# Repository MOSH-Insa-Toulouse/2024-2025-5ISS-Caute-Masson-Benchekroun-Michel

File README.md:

**Repository structure :**
- [LoRa\_module.ino](LoRa_module.ino) : Smart device code, from the logic for using the gas sensor, to the BLE and LoRa connectivity.
- [Shield\_Gas\_Sensor](Shield_Gas_Sensor) : Design of the Arduino UNO shield for the smart device. See the routing [here](Shield_Gas_Sensor/Acquisition_board_aduino_UNO.kicad_pcb), and the schematic [here](Shield_Gas_Sensor/Acquisition_board_aduino_UNO.kicad_sch)
- [Node-RED](Node-RED) : Node RED application code
- [Documentation](Documentation) : Datasheet of the used components
- [The datasheet](Datasheet_Gas_Sensor.pdf) : Datasheet of our gas sensor
- [The project report](MOSH_Report.pdf) : Report of our smart device project, from the manufacturing of the MOx sensor to the design of our node PCB, sensor conditionner and application

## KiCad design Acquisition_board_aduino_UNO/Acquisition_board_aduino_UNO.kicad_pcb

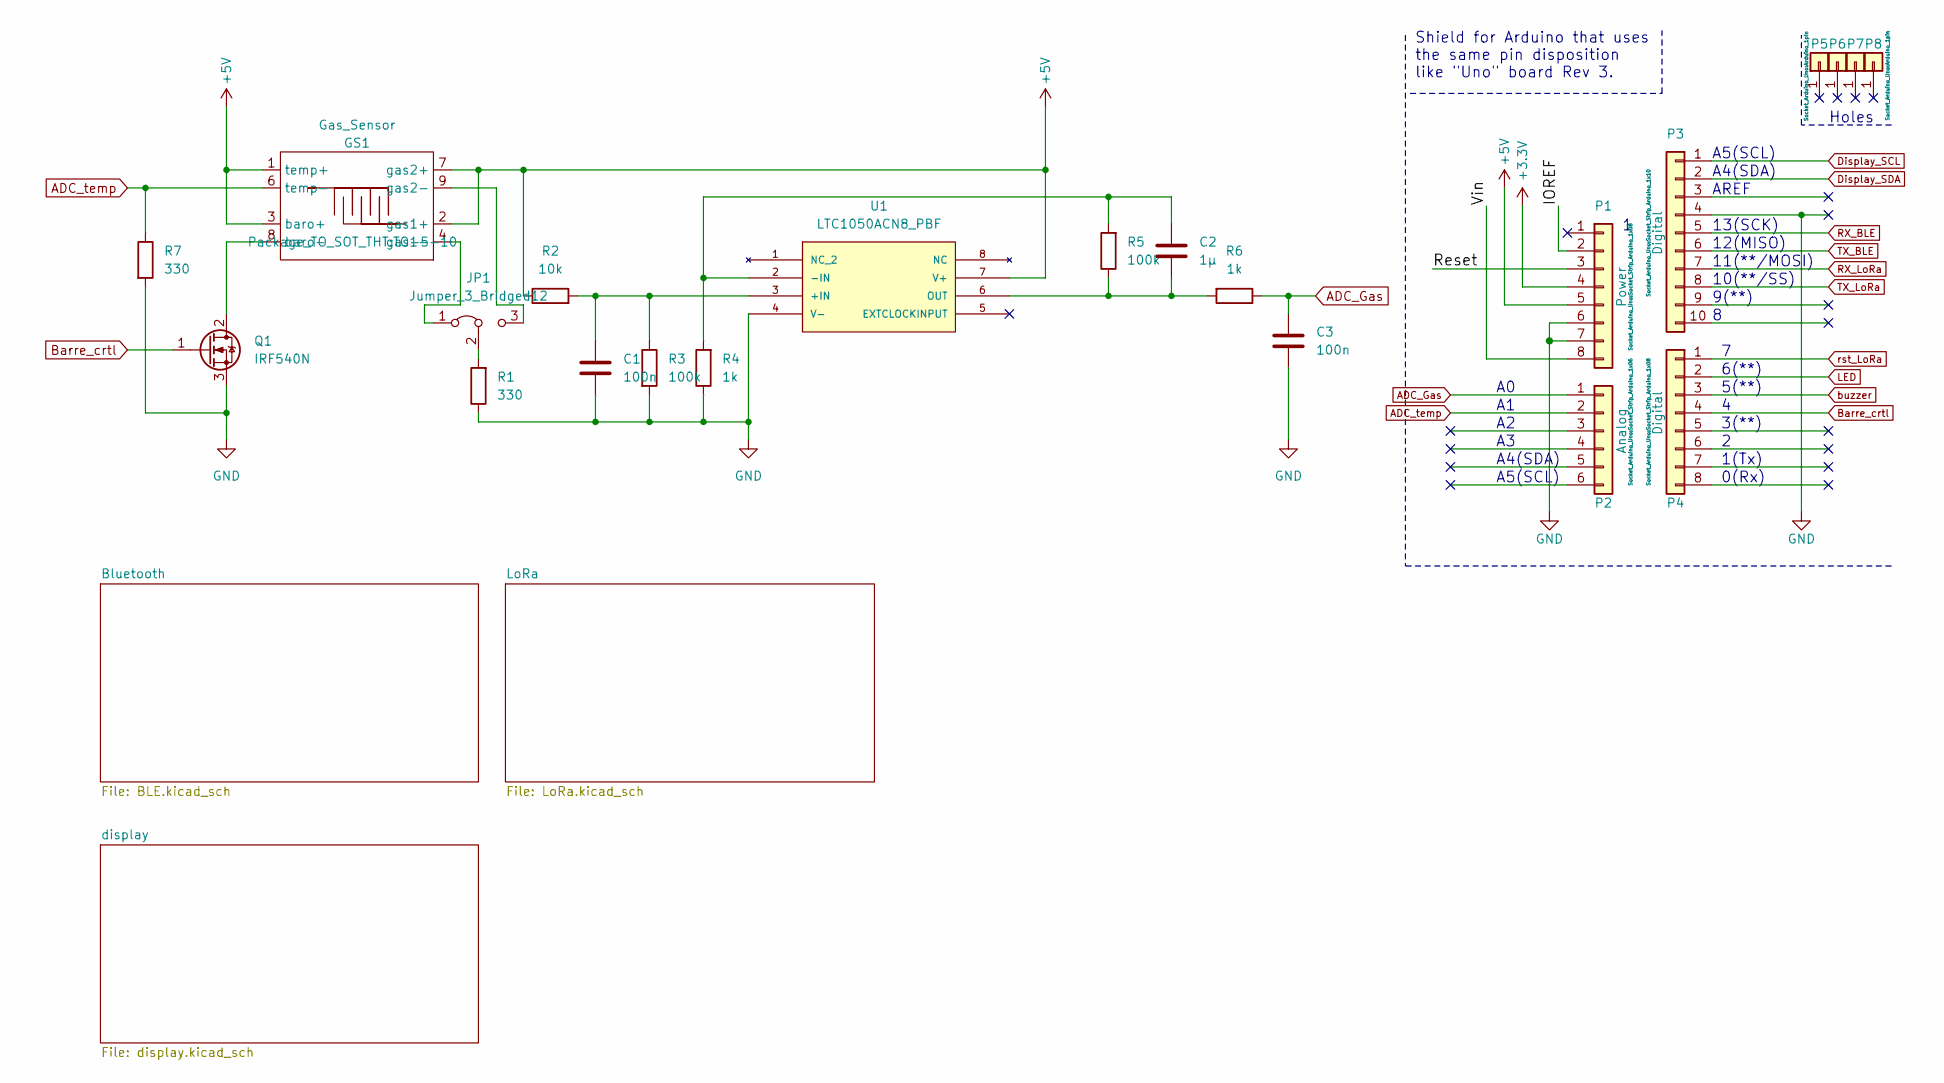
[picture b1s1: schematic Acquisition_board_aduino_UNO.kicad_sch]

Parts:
C1, C3: 100n; C_Disc_D3.0mm_W1.6mm_P2.50mm
C2: 1µ; C_Rect_L9.0mm_W3.6mm_P7.50mm_MKT
GS1: Gas_Sensor; TO-5-10
JP1: Jumper_3_Bridged12; PinSocket_1x03_P2.54mm_Vertical
P1: Power; Socket_Strip_Arduino_1x08
P2: Analog; Socket_Strip_Arduino_1x06
P3: Digital; Socket_Strip_Arduino_1x10
P4: Digital; Socket_Strip_Arduino_1x08
P5, P6, P7, P8: CONN_01X01; Arduino_1pin
Q1: IRF540N; TO-220-3_Vertical
R1, R7: 330; R_Axial_DIN0204_L3.6mm_D1.6mm_P2.54mm_Vertical
R2: 10k; R_Axial_DIN0204_L3.6mm_D1.6mm_P2.54mm_Vertical
R3, R5: 100k; R_Axial_DIN0204_L3.6mm_D1.6mm_P2.54mm_Vertical
R4, R6: 1k; R_Axial_DIN0204_L3.6mm_D1.6mm_P2.54mm_Vertical
U1: LTC1050ACN8_PBF; DIP-8_W7.62mm; MANUFACTURER_PART_NUMBER ltc1050acn8

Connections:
+3V3: P1.4
+5V: GS1.1 (temp+), GS1.2 (gas1+), GS1.3 (baro+), GS1.7 (gas2+), P1.5, R2.1, U1.7 (V+); also elsewhere on the board
/IOREF: P1.2
/Reset: P1.3
/Vin: P1.8
ADC_Gas: C3.1, P2.1, R6.1
ADC_temp: GS1.6 (temp-), P2.2, R7.1
Barre_crtl: P4.4, Q1.1 (G)
Display_SCL: P3.1; also elsewhere on the board
Display_SDA: P3.2; also elsewhere on the board
GND: C1.2, C3.2, P1.6, P1.7, P3.4, P5.1, P6.1, P7.1, P8.1, Q1.3 (S), R1.1, R3.2, R4.1, R7.2, U1.4 (V-); also elsewhere on the board
LED: P4.2; also elsewhere on the board
unnamed: C1.1, R2.2, R3.1, U1.3 (+IN)
unnamed: C2.1, R4.2, R5.2, U1.2 (-IN)
unnamed: C2.2, R5.1, R6.2, U1.6 (OUT)
unnamed: GS1.4 (gas1-), JP1.1 (A)
unnamed: GS1.8 (baro-), Q1.2 (D)
unnamed: GS1.9 (gas2-), JP1.3 (B)
unnamed: JP1.2 (C), R1.2
RX_BLE: P3.5; also elsewhere on the board
RX_LoRa: P3.7; also elsewhere on the board
TX_BLE: P3.6; also elsewhere on the board
TX_LoRa: P3.8; also elsewhere on the board
buzzer: P4.3; also elsewhere on the board
rst_LoRa: P4.1; also elsewhere on the board

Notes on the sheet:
A5(SCL)
6(**)
10(**/SS)
3(**)
0(Rx)
9(**)
Holes
1(Tx)
Shield for Arduino that uses the same pin disposition like "Uno" board Rev 3.
5(**)
12(MISO)
A4(SDA)
AREF
13(SCK)
11(**/MOSI)

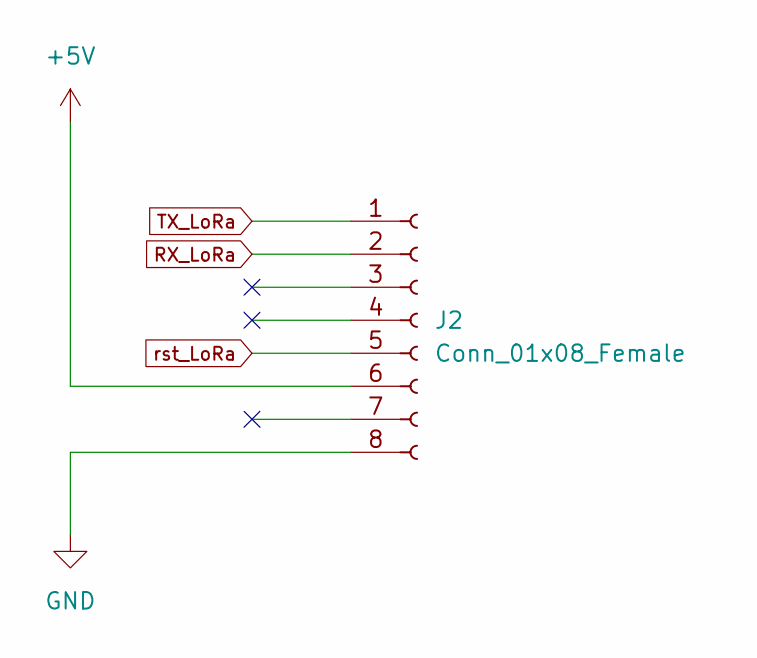
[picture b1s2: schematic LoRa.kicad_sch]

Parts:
J2: Conn_01x08_Female; PinSocket_1x08_P2.54mm_Vertical

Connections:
+5V: J2.6; also elsewhere on the board
GND: J2.8; also elsewhere on the board
RX_LoRa: J2.2; also elsewhere on the board
TX_LoRa: J2.1; also elsewhere on the board
rst_LoRa: J2.5; also elsewhere on the board

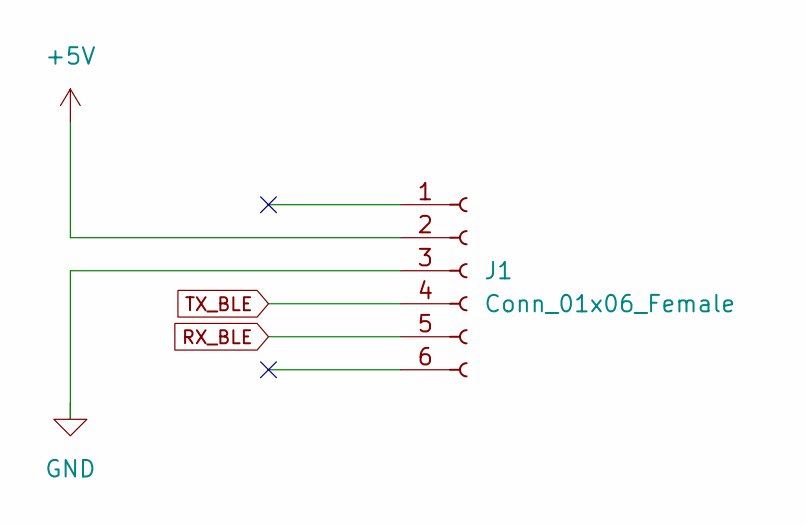
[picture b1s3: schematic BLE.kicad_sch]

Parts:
J1: Conn_01x06_Female; PinSocket_1x06_P2.54mm_Vertical

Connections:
+5V: J1.2; also elsewhere on the board
RX_BLE: J1.5; also elsewhere on the board
TX_BLE: J1.4; also elsewhere on the board

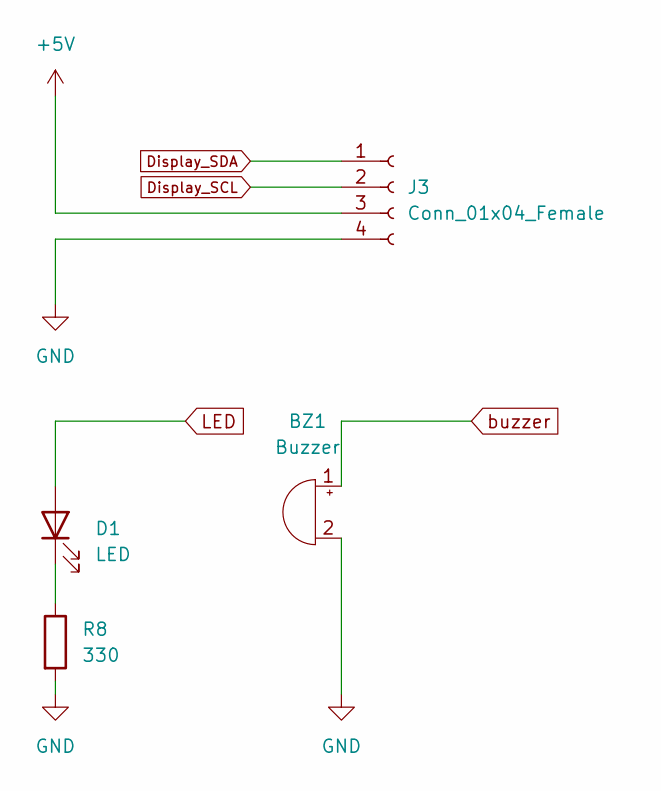
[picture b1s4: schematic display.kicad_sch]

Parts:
BZ1: Buzzer; Buzzer_TDK_PS1240P02BT_D12.2mm_H6.5mm
D1: LED; LED_D3.0mm
J3: Conn_01x04_Female; PinSocket_1x04_P2.54mm_Vertical
R8: 330; R_Axial_DIN0204_L3.6mm_D1.6mm_P2.54mm_Vertical

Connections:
+5V: J3.3; also elsewhere on the board
Display_SCL: J3.2; also elsewhere on the board
Display_SDA: J3.1; also elsewhere on the board
GND: BZ1.2 (+), J3.4, R8.2; also elsewhere on the board
LED: D1.2 (A); also elsewhere on the board
unnamed: D1.1 (K), R8.1
buzzer: BZ1.1 (-); also elsewhere on the board

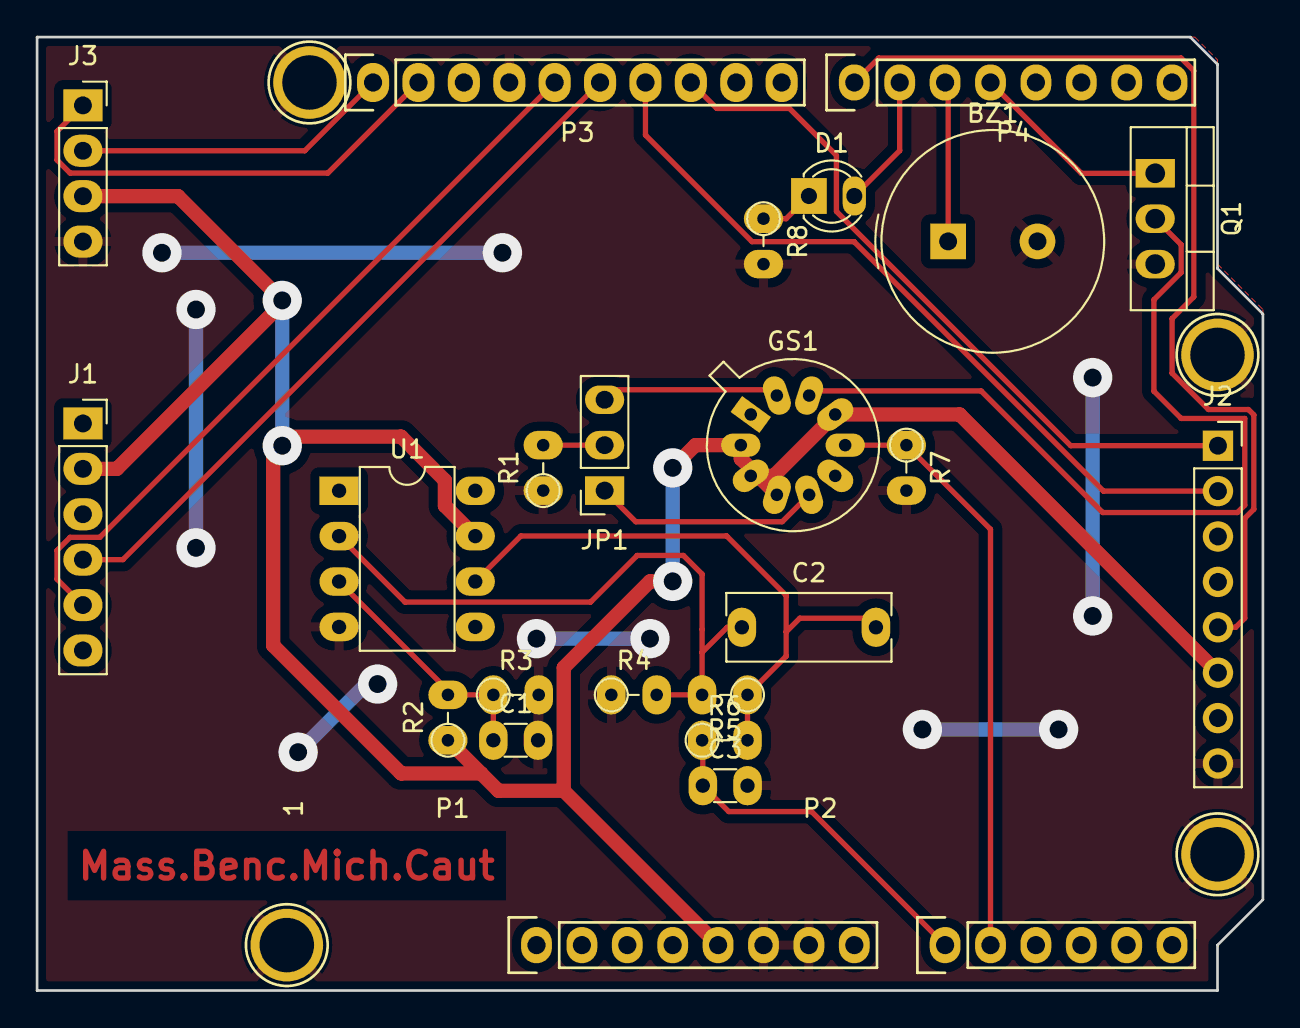
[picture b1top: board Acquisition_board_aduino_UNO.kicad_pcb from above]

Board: 2 copper layers, 68.6 x 53.3 mm, 28 parts (0 on the bottom side), 22 nets.

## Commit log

2024-12-17 lora test do not work
2024-12-17 Create Node-RED flows
2024-12-18 Create Node-red
2024-12-18 Create node
2024-12-18 schematic finished
2025-01-29 routing n schematic
2025-01-29 report
2025-01-29 Datasheet
2025-01-29 Documentation
2025-01-29 Add the code for the Arduino
2025-01-29 cleaning
2025-01-29 cleaning_2
2025-01-29 README

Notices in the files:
parts and their libraries:
COPYRIGHT: Copyright C 2016 Accelerated Designs. All rights reserved
